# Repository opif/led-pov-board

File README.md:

LED Persistance-of-Vision

KiCAD project files for the board used with [LED-PoV](https://github.com/opif/led-pov).

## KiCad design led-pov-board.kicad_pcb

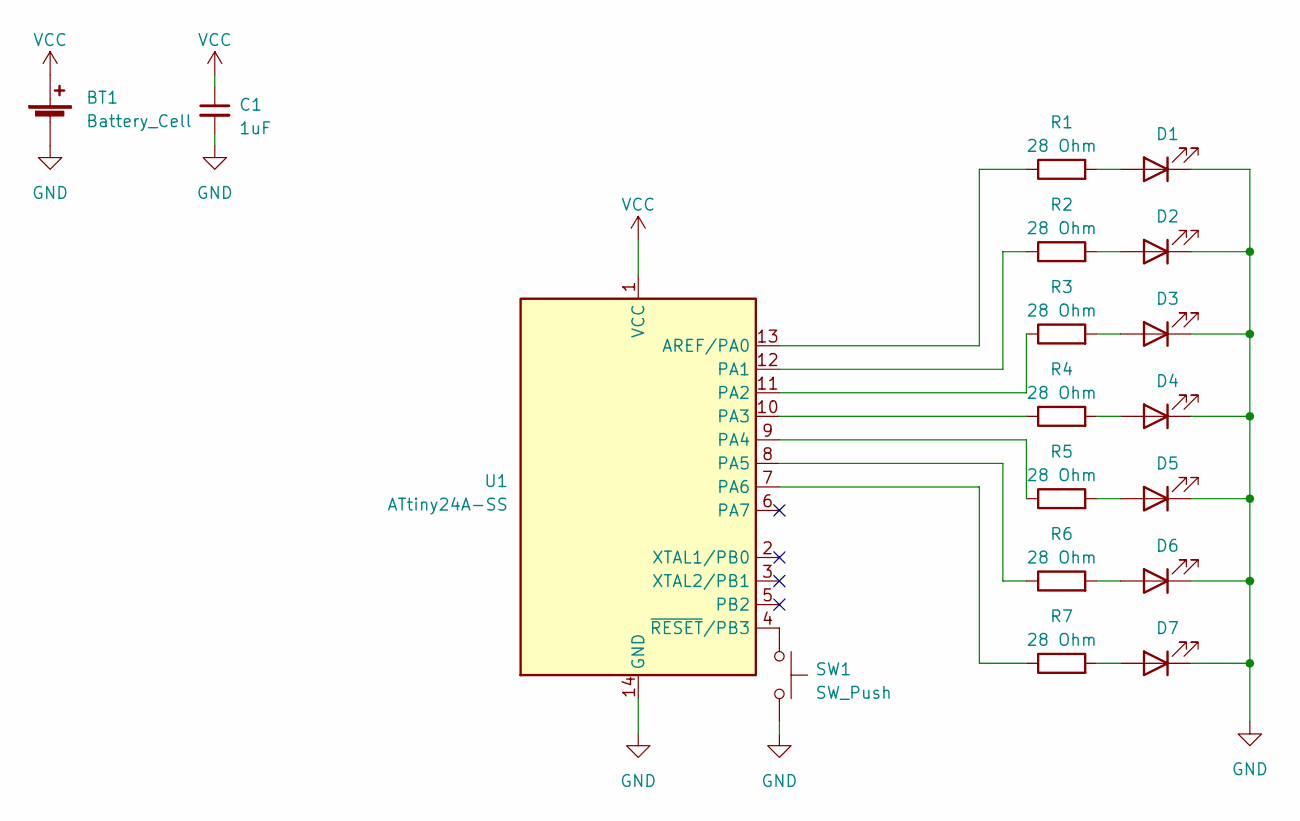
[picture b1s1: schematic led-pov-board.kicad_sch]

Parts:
BT1: Battery_Cell; BatteryHolder_ComfortableElectronic_CH273-2450_1x2450
C1: 1uF; C_0805_2012Metric_Pad1.18x1.45mm_HandSolder
D1, D2, D3, D4, D5, D6, D7: LED; LED_PLCC_2835_Handsoldering
R1, R2, R3, R4, R5, R6, R7: 28 Ohm; R_1206_3216Metric_Pad1.30x1.75mm_HandSolder
SW1: SW_Push; Panasonic_EVQPUJ_EVQPUA
U1: ATtiny24A-SS; SOIC-14_3.9x8.7mm_P1.27mm

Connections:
GND: BT1.2 (-), C1.2, D1.1 (K), D2.1 (K), D3.1 (K), D4.1 (K), D5.1 (K), D6.1 (K), D7.1 (K), SW1.2, U1.14 (GND)
unnamed: D1.2 (A), R1.2
unnamed: D2.2 (A), R2.2
unnamed: D3.2 (A), R3.2
unnamed: D4.2 (A), R4.2
unnamed: D5.2 (A), R5.2
unnamed: D6.2 (A), R6.2
unnamed: D7.2 (A), R7.2
unnamed: R1.1, U1.13 (AREF/PA0)
unnamed: R2.1, U1.12 (PA1)
unnamed: R3.1, U1.11 (PA2)
unnamed: R4.1, U1.10 (PA3)
unnamed: R5.1, U1.9 (PA4)
unnamed: R6.1, U1.8 (PA5)
unnamed: R7.1, U1.7 (PA6)
unnamed: SW1.1, U1.4 (~RESET/PB3)
VCC: BT1.1 (+), C1.1, U1.1 (VCC)

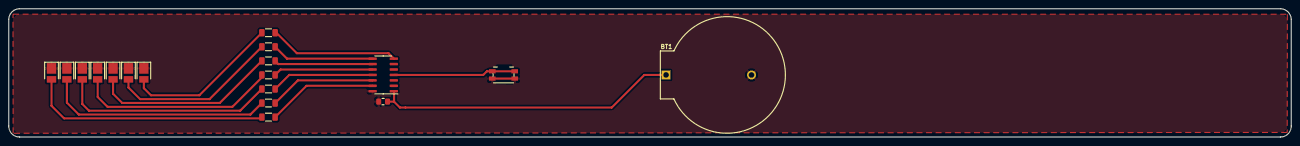
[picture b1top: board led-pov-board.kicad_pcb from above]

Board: 2 copper layers, 300.0 x 30.0 mm, 18 parts (0 on the bottom side), 17 nets.

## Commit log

2023-04-04 initial
2023-04-04 first version
2023-04-04 add readme
2023-04-27 add details to schematic
